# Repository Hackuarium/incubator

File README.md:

# Cheap and simple incubator

Can we do a simple incubator that is actually more advanced than the commercial one ?

The idea of this project is to create the hardware that allows to control a peltier
thermoelectric module in order to warm or cool down a closed space.

In order to make an incubator we want to use any polystyrene box, make a hole and
insert a module.

A smart control should allow precise control of the temperature not only to warm up
but also to cool down and to define a temperature program. Like that you could incubate
couple of culture plate at 37°C the Friday evening and program the incubator so 
that it cools down to 4°C after 24h.

Well this is still a work in progress. The PCB in done and functional. The fun starts now !

## Cloning the project

In order to clone it use:

git clone --recurse-submodules https://github.com/hackuarium/incubator

To update the submodules:

git submodule update --recursive --remote

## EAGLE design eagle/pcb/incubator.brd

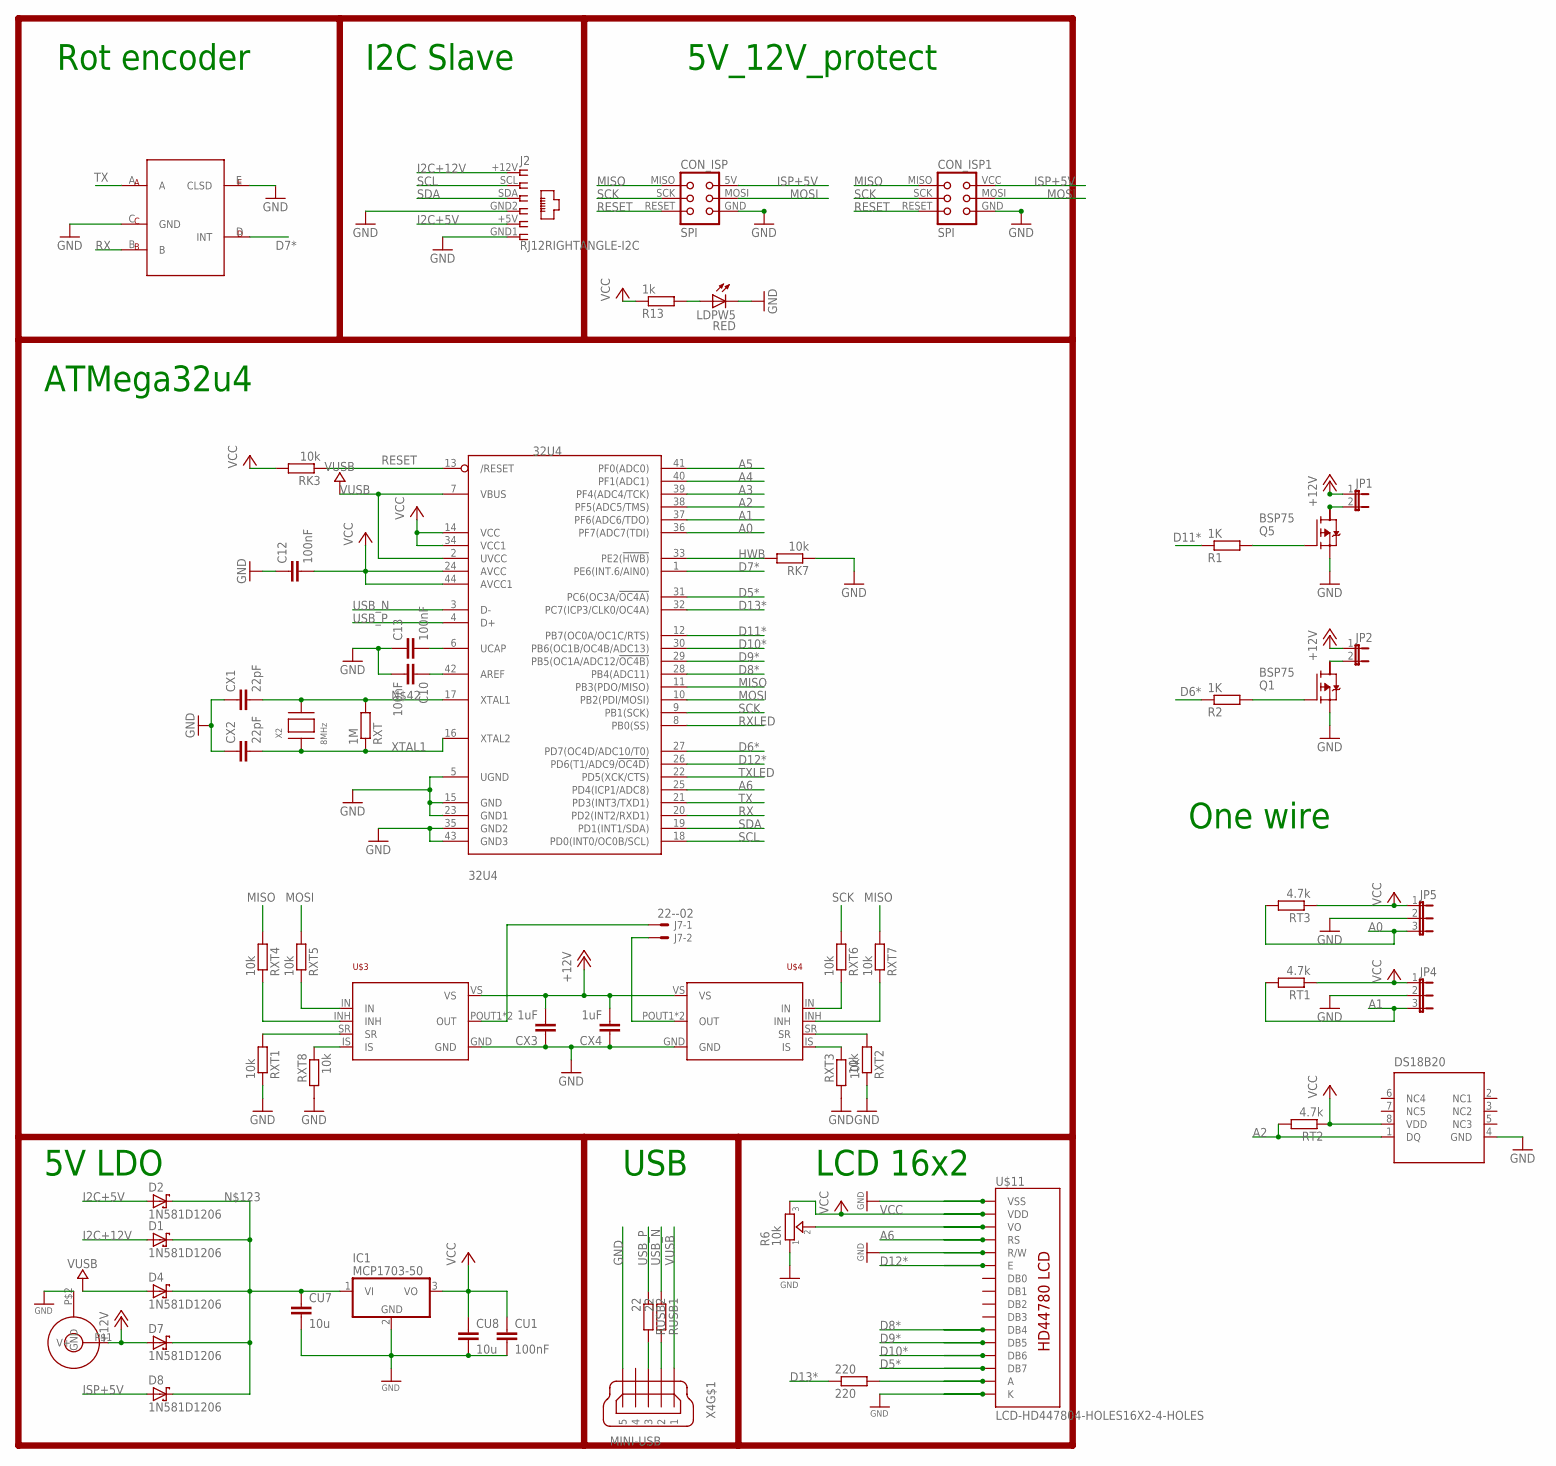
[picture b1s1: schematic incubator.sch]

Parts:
32U4: 32U4; TQFP44
220: 220; R0805
C10, C12, C13: 100nF; C0805
CON_ISP: SPI; TC2030-MCP-NL
CON_ISP1: SPI; TINYISP
CU1: 100nF; C0805
CU7, CU8: 10u; C0805
CX1, CX2: 22pF; C0805
CX3, CX4: 1uF; C0805
D1, D2, D4, D7, D8: 1N581D1206; LED-1206
IC1: MCP1703-50; SOT223
J2: RJ12RIGHTANGLE-I2C; RJ12-RIGHTANGLE-I2C
J7: 22--02; 2-PIN-5.08S
JP1, JP2: JUMPER-2PTH; 1X02
JP4, JP5: JP2E; JP2
LDPW5: RED; CHIP-LED0805
POWER: JACK_DC_BARREL; DC_BARREL
Q1, Q5: BSP75; PG-SOT-223
R1, R2: 1K; R0805
R6: 10k; TRIMMER_3362P
R13: 1k; R0805
RK3, RK7: 10k; M0805
RT1, RT2, RT3: 4.7k; R0805
RUSB1, RUSB2: 22; M0805
RXT: 1M; R0805
RXT1, RXT2, RXT3, RXT4, RXT5, RXT6, RXT7, RXT8: 10k; R0805
U$1: ROTARYENCODER
U$3, U$4: BTS7960; P-TO-263-7
U$5: DS18B20; MSOP8
U$11: LCD-HD447804-HOLES16X2-4-HOLES; LCD-16X2-4HOLES
X2: 8MHz; NX6035
X4: MINI-USB; 32005-201

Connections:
+12V: CX3.2, CX4.2, D7.A, JP1.1, JP2.1, POWER.P$1 (V+), U$3.VS, U$4.VS
A0: 32U4.36 (PF7(ADC7(TDI)), JP5.3, RT3.2
A1: 32U4.37 (PF6(ADC6/TDO)), JP4.3, RT1.2
A2: 32U4.38 (PF5(ADC5/TMS)), RT2.2, U$5.1 (DQ)
A3: 32U4.39 (PF4(ADC4/TCK))
A4: 32U4.40 (PF1(ADC1))
A5: 32U4.41 (PF0(ADC0))
A6: 32U4.25 (PD4(ICP1/ADC8)), U$11.4 (RS)
AREF: 32U4.42 (AREF), C10.1
D5*: 32U4.31 (PC6(OC3A/!OC4A)), U$11.14 (DB7)
D6*: 32U4.27 (PD7(OC4D/ADC10/T0)), R2.1
D7*: 32U4.1 (PE6(INT.6/AIN0)), U$1.D (INT)
D8*: 32U4.28 (PB4(ADC11)), U$11.11 (DB4)
D9*: 32U4.29 (PB5(OC1A/ADC12/!OC4B)), U$11.12 (DB5)
D10*: 32U4.30 (PB6(OC1B/OC4B/ADC13)), U$11.13 (DB6)
D11*: 32U4.12 (PB7(OC0A/OC1C/RTS)), R1.1
D12*: 32U4.26 (PD6(T1/ADC9/!OC4D)), U$11.6 (E)
D13*: 32U4.32 (PC7(ICP3/CLK0/OC4A)), 220.1
GND: 32U4.5 (UGND), 32U4.15 (GND), 32U4.23 (GND1), 32U4.35 (GND2), 32U4.43 (GND3), C10.2, C12.1, C13.1, CON_ISP.GND, CON_ISP1.GND, CU1.2, CU7.2, CU8.2, CX1.1, CX2.1, CX3.1, CX4.1, IC1.2 (GND), J2.GND1 (6), J2.GND2 (4), JP4.2, JP5.2, LDPW5.C, POWER.P$2 (GND), Q1.3 (S), Q5.3 (S), R6.1, RK7.1, RXT1.1, RXT2.1, RXT3.2, RXT8.2, U$1.C (GND), U$1.E (CLSD), U$3.GND, U$4.GND, U$5.4 (GND), U$11.1 (VSS), U$11.5 (R/W), U$11.16 (K), X4.5
HWB: 32U4.33 (PE2(!HWB)), RK7.2
I2C+5V: D2.A, J2.+5V (5)
I2C+12V: D1.A, J2.+12V (1)
ISP+5V: CON_ISP.5V (VCC), CON_ISP1.VCC, D8.A
MISO: 32U4.11 (PB3(PDO/MISO)), CON_ISP.MISO, CON_ISP1.MISO, RXT4.2, RXT7.2
MOSI: 32U4.10 (PB2(PDI/MOSI)), CON_ISP.MOSI, CON_ISP1.MOSI, RXT5.2
unnamed: 32U4.6 (UCAP), C13.2
unnamed: R6.2, U$11.3 (VO)
unnamed: RXT5.1, U$3.IN
unnamed: RXT6.1, U$4.IN
unnamed: RXT4.1, U$3.INH
unnamed: RXT7.1, U$4.INH
unnamed: RXT3.1, U$4.IS
unnamed: Q5.1 (G), R1.2
unnamed: RXT2.2, U$4.SR
unnamed: 220.2, U$11.15 (A)
unnamed: LDPW5.A, R13.2
unnamed: RXT1.2, U$3.SR
unnamed: RXT8.1, U$3.IS
unnamed: J7.1, U$3.POUT1 (OUT), U$3.POUT2 (OUT)
unnamed: Q1.1 (G), R2.2
unnamed: JP1.2, Q5.2 (D)
unnamed: J7.2, U$4.POUT1 (OUT), U$4.POUT2 (OUT)
unnamed: JP2.2, Q1.2 (D)
unnamed: 32U4.17 (XTAL1), CX1.2, RXT.2, X2.P$2
unnamed: CU7.1, D1.C, D2.C, D4.C, D7.C, D8.C, IC1.1 (VI)
RESET: 32U4.13 (/RESET), CON_ISP.RESET, CON_ISP1.RESET, RK3.1
RX: 32U4.20 (PD2(INT2/RXD1)), U$1.B
RXLED: 32U4.8 (PB0(SS))
SCK: 32U4.9 (PB1(SCK)), CON_ISP.SCK, CON_ISP1.SCK, RXT6.2
SCL: 32U4.18 (PD0(INT0/OC0B/SCL)), J2.SCL (2)
SDA: 32U4.19 (PD1(INT1/SDA)), J2.SDA (3)
TX: 32U4.21 (PD3(INT3/TXD1)), U$1.A
TXLED: 32U4.22 (PD5(XCK/CTS))
USBC_N: RUSB1.2, X4.2
USBC_P: RUSB2.2, X4.3
USB_N: 32U4.3 (D-), RUSB1.1
USB_P: 32U4.4 (D+), RUSB2.1
VCC: 32U4.14 (VCC), 32U4.24 (AVCC), 32U4.34 (VCC1), 32U4.44 (AVCC1), C12.2, CU1.1, CU8.1, IC1.3 (VO), JP4.1, JP5.1, R6.3, R13.1, RK3.2, RT1.1, RT2.1, RT3.1, U$5.8 (VDD), U$11.2 (VDD)
VUSB: 32U4.2 (UVCC), 32U4.7 (VBUS), D4.A, X4.1
XTAL1: 32U4.16 (XTAL2), CX2.2, RXT.1, X2.P$1

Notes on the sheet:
USB
5V_12V_protect
ATMega32u4
I2C Slave
LCD 16x2
Rot encoder
5V LDO
One wire

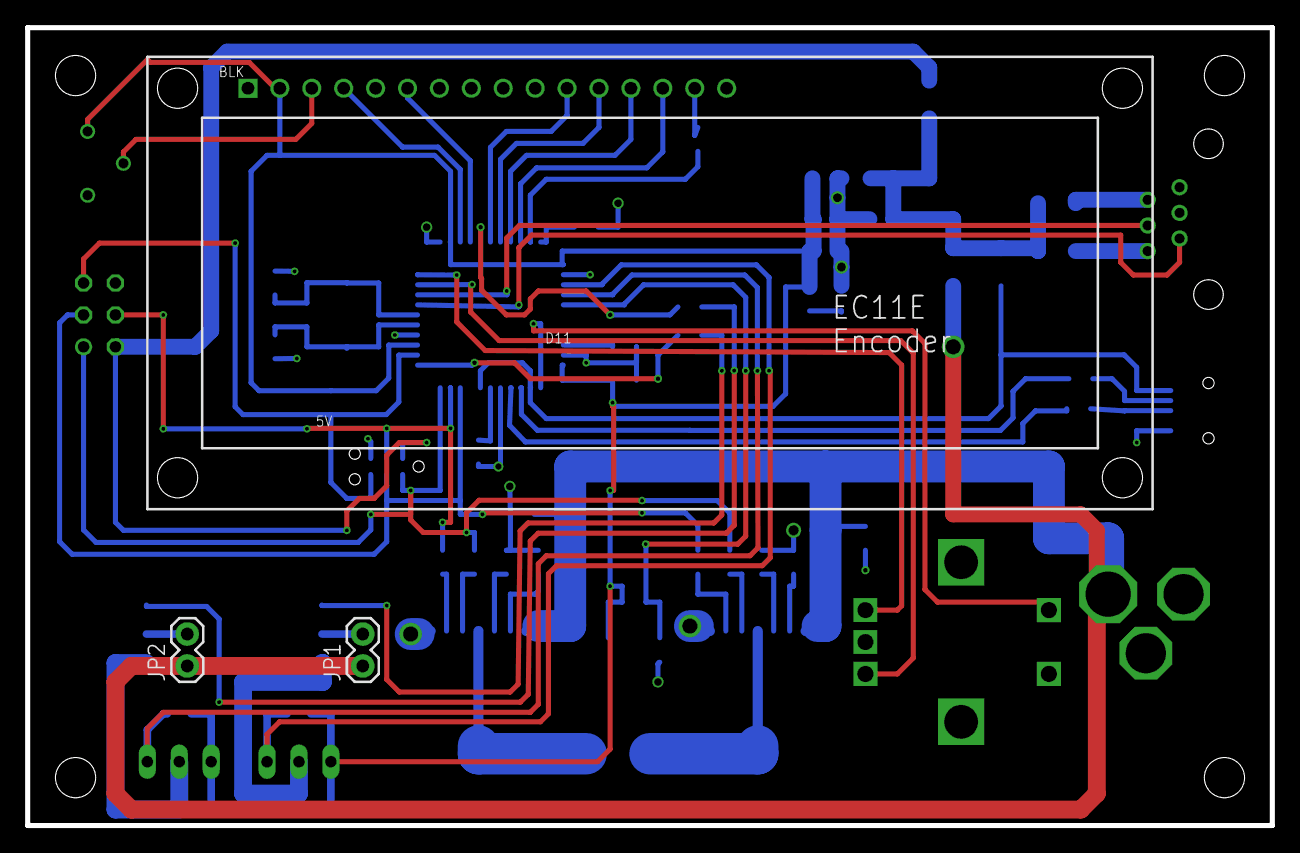
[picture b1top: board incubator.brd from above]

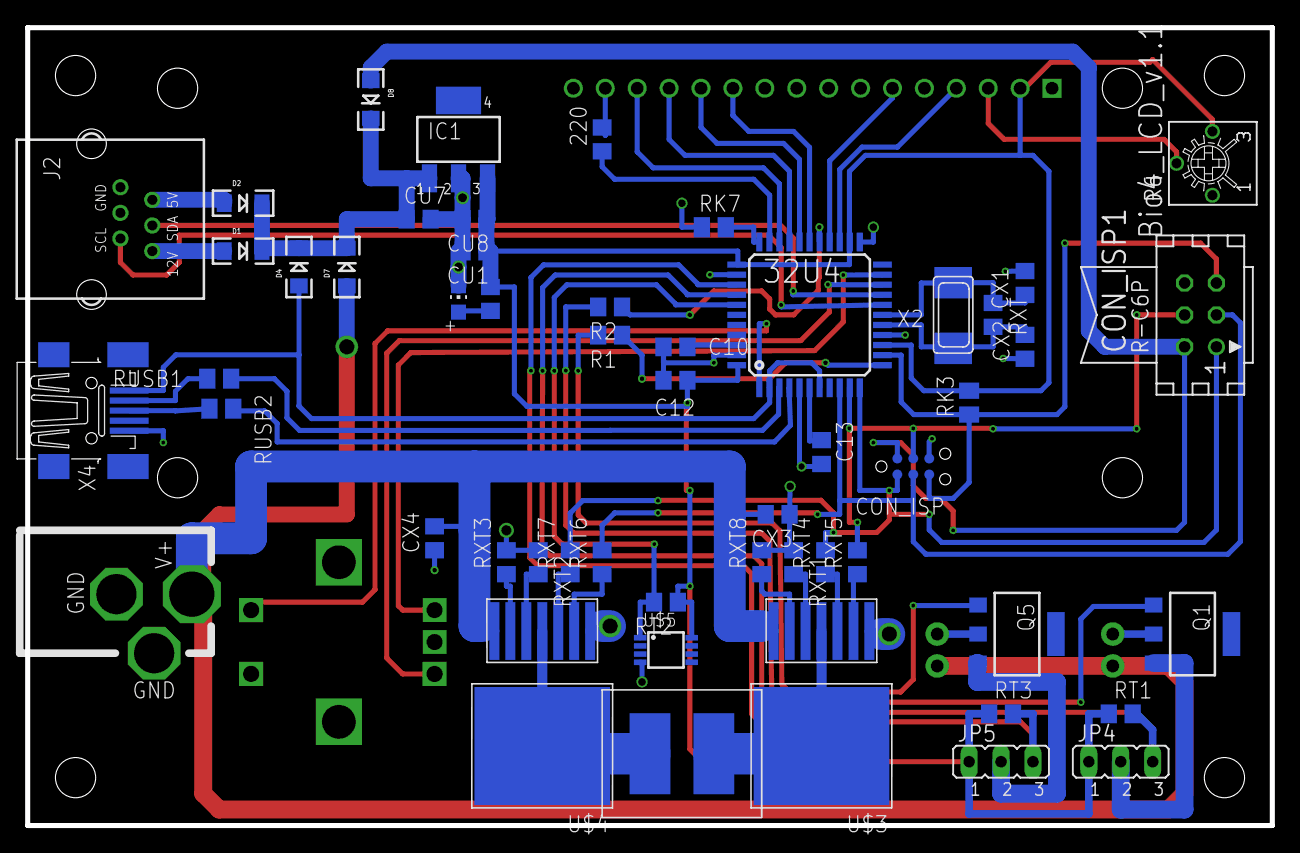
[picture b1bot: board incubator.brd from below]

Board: 4 copper layers, 99.1 x 63.5 mm, 57 parts (53 on the bottom side), 55 nets.

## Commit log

2017-07-08 First design thinking
2017-08-09 routing in progress
2017-08-14 first version of the incubator
2017-09-23 add test case and begin arduino program
2017-09-29 working on PID
2018-12-04 Library for new Rotary Encoder designed by Hans
2018-12-04 changed name to Rotary Encoder
2018-12-11 45 degree traces
2018-12-11 add l#* in gitignore
2018-12-11 add .DS_Store in gitignore
2018-12-11 version 1.1
2019-01-22 version 1.1.0
2019-03-19 working on new arduino for version 1.1.0
2019-03-26 update of code
2019-03-27 add libino
2019-03-27 add error
2019-03-27 add saveAndLogError
2019-03-29 improve OneWire and Lcd
2019-03-29 update lcd program
2019-03-30 add logger
2020-04-05 chore: add info about submodules
2020-04-11 fix: fix manuy parameters bugs
2020-04-11 working version

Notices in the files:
parts and their libraries:
lpatiny: ©2009 ROFA.cz - modified and updated by Robert Darlington ‹rdarlington@gmail.com›
SparkFun: Licensing: CC v3.0 Share-Alike You are welcome to use this library for commercial purposes.
